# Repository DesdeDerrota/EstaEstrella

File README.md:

# EstaEstrella
Building my own iteration of a Starbie as a beginner project.

First off, what is a Starbie?
----------------------------------------

A Starbie is a little nickname used to describe the HackClub creation of the week, 
a tamagotchi like device capable of interacting with the user. It's named a Starbie 
for copyright reasons (takes some creative liberties from the device known as a 
Starboy, image below.

(Image Reference in the Alt Text)

Why make a Starbie?
----------------------------------------

I made a Starbie as apart of a multiweek challenge for Hack Club, the Starbie being the beginner project for the week 1 of Half Life, 
the name of the challenge. While I do have experience with hardware to some degree, to be frank, I have a lot to learn, so I chose
Starbie as a means to improve my skills.

Challenges
----------------------------------------

Along this journey, I had numerous, numerous, problems, all of which stemmed from ineptness. To create my project, I had to learn,
or understand, how to utilize the tools of KiCAD. KiCAD, for those who don't understand, is a computer aided circuit modeling software
which allows one to create a circuit, on the PCB's we all know and love. PCB, also for those who don't understand, stands for Printed
Circuit Board (covering all the bases, I think that I would appreciate it if I was younger). Using the designs provided by the wonderous
SharKing Studios, who designed the Starbie, I had to essentially follow the order and structure of the board he made. Sounds easy, until
put in practice, and the smallest error is what sets you back for about and hour or so (I know, it happened more than I want to admit).

Personal Touches
----------------------------------------
- The board has been modified to be squared and rounded.
- The PCB has two, non function related slots which serve to fit the board into a custom case.
- The character in the PCB is custom, made from a previous project and imported into the bitmap format.

Credits & Original Design
----------------------------------------

Click the Image to See the Source (published by The Great SharKing Studios)

BOM (Linked Below)
----------------------------------------
<a href="BOM.csv">BOM</a>

Conclusion
----------------------------------------
10/10 Experience, regardless of the frustration, would do again. :)

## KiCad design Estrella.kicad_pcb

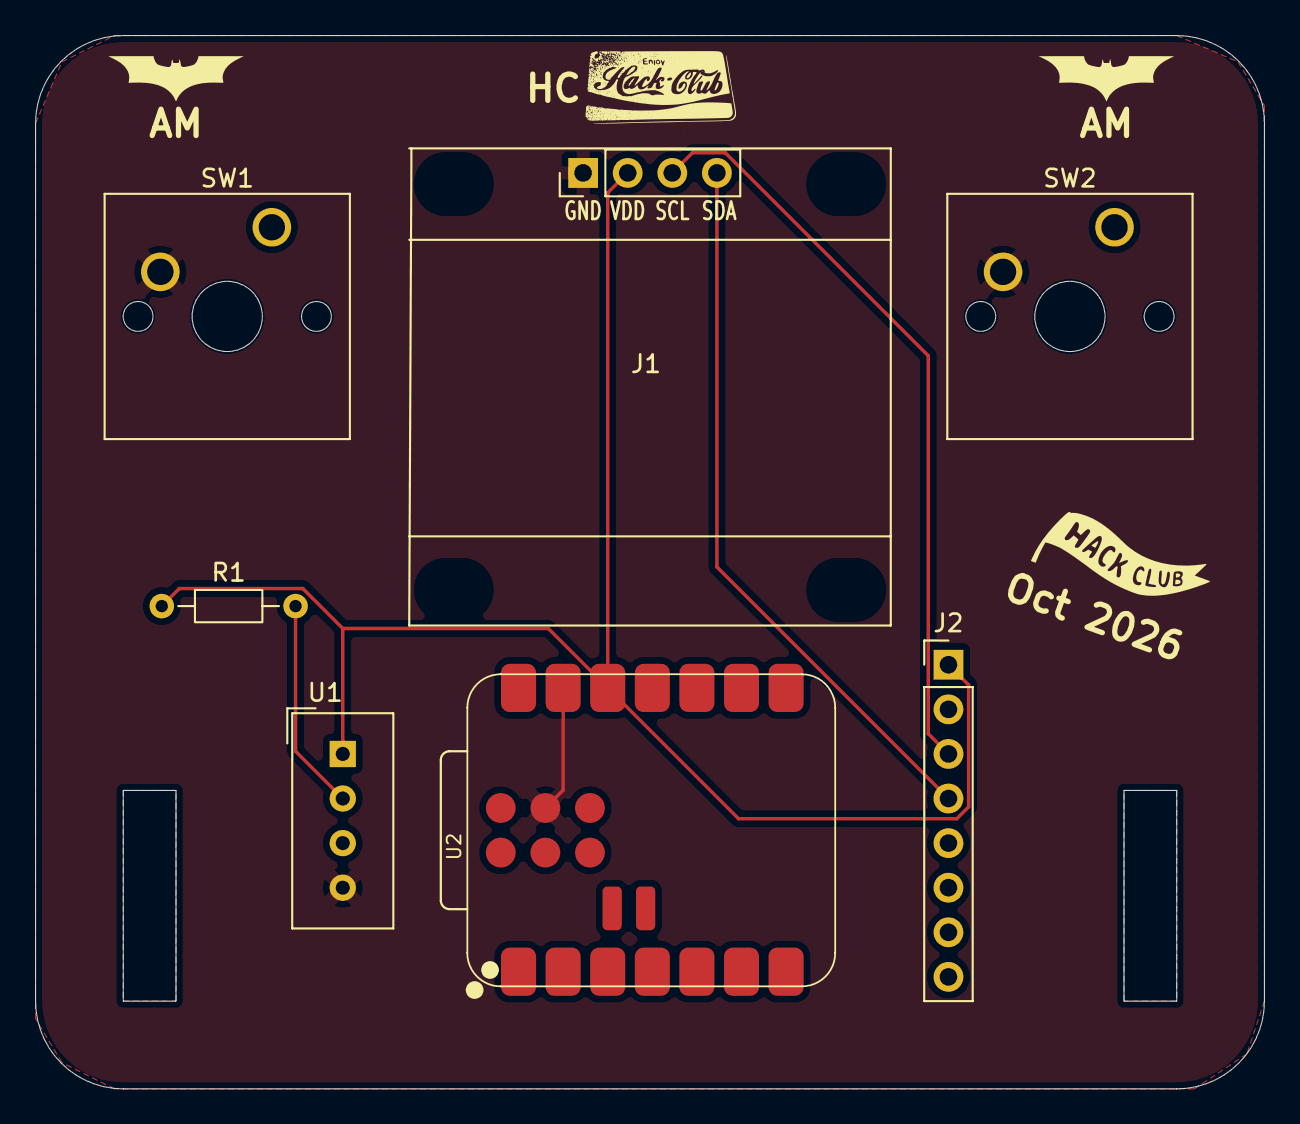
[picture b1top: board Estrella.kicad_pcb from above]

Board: 2 copper layers, 70.0 x 60.0 mm, 11 parts (0 on the bottom side), 5 nets.

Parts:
AM: LOGO
AM#2: LOGO
HC: LOGO
J1: Conn_01x04_Pin; Display_128x64_096_I2C
J2: Conn_01x08_Pin; PinHeader_1x08_P2.54mm_Vertical
Oct 2026: LOGO
R1: 10k; R_Axial_DIN0204_L3.6mm_D1.6mm_P7.62mm_Horizontal
SW1, SW2: SW_Push; SW_Cherry_MX_1.00u_PCB
U1: DHT11; Aosong_DHT11_5.5x12.0_P2.54mm
U2: XIAO-ESP32-C3-SMD

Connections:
+3.3V: J1.2, J2.1, R1.1, U1.1 (VDD), U2.12 (3V3_OUT)
/DHT11 DATA: R1.2, U1.2 (DATA)
/SCL: J1.3, J2.3
/SDA: J1.4, J2.4
GND: J1.1, J2.2, SW1.2, SW2.2, U1.4 (GND), U2.13 (GND), U2.18 (GND)
